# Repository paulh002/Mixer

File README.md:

# Mixer
Simple double balanced mixer and diplexer

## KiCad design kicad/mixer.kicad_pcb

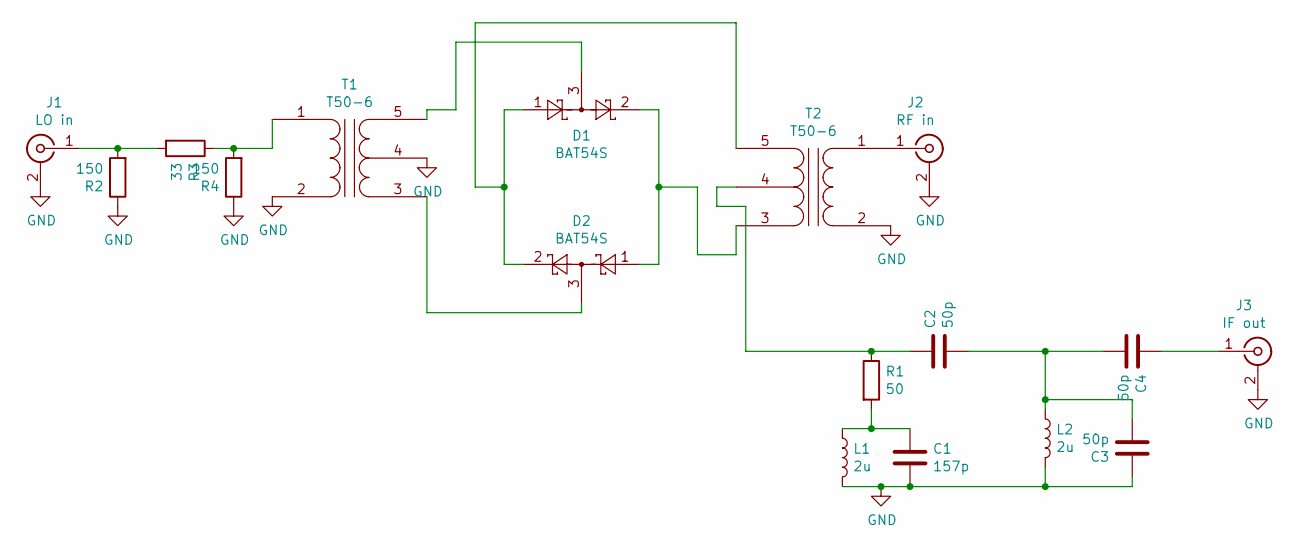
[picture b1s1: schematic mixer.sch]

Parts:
C1: 157p; C_1206_3216Metric_Pad1.42x1.75mm_HandSolder
C2, C3, C4: 50p; C_1206_3216Metric_Pad1.42x1.75mm_HandSolder
D1, D2: BAT54S; SOT-23
J1: LO in; SMA_Amphenol_132134_Vertical
J2: RF in; SMA_Amphenol_132134_Vertical
J3: IF out; SMA_Amphenol_132134_Vertical
L1, L2: 2u; Transformer_Toroid_Horizontal_3S_D14.0mm_Amidon-T50
R1: 50; R_1206_3216Metric_Pad1.42x1.75mm_HandSolder
R2, R4: 150; R_1206_3216Metric_Pad1.42x1.75mm_HandSolder
R3: 33; R_1206_3216Metric_Pad1.42x1.75mm_HandSolder
T1, T2: T50-6; Transformer_Toroid_Horizontal_3S_D14.0mm_Amidon-T50

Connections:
GND: C1.2, C3.1, J1.2 (Ext), J2.2 (Ext), J3.2 (Ext), L1.2, L2.2, R2.1, R4.1, T1.2 (AB), T1.4 (SC), T2.2 (AB)
unnamed: C1.1, L1.1, R1.2
unnamed: C2.1, R1.1, T2.4 (SC)
unnamed: C2.2, C3.2, C4.2, L2.1
unnamed: C4.1, J3.1 (In)
unnamed: D1.1, D2.2, T2.5 (SB)
unnamed: D1.2, D2.1, T2.3 (SA)
unnamed: D1.3, T1.5 (SB)
unnamed: D2.3, T1.3 (SA)
unnamed: J1.1 (In), R2.2, R3.2
unnamed: J2.1 (In), T2.1 (AA)
unnamed: R3.1, R4.2, T1.1 (AA)

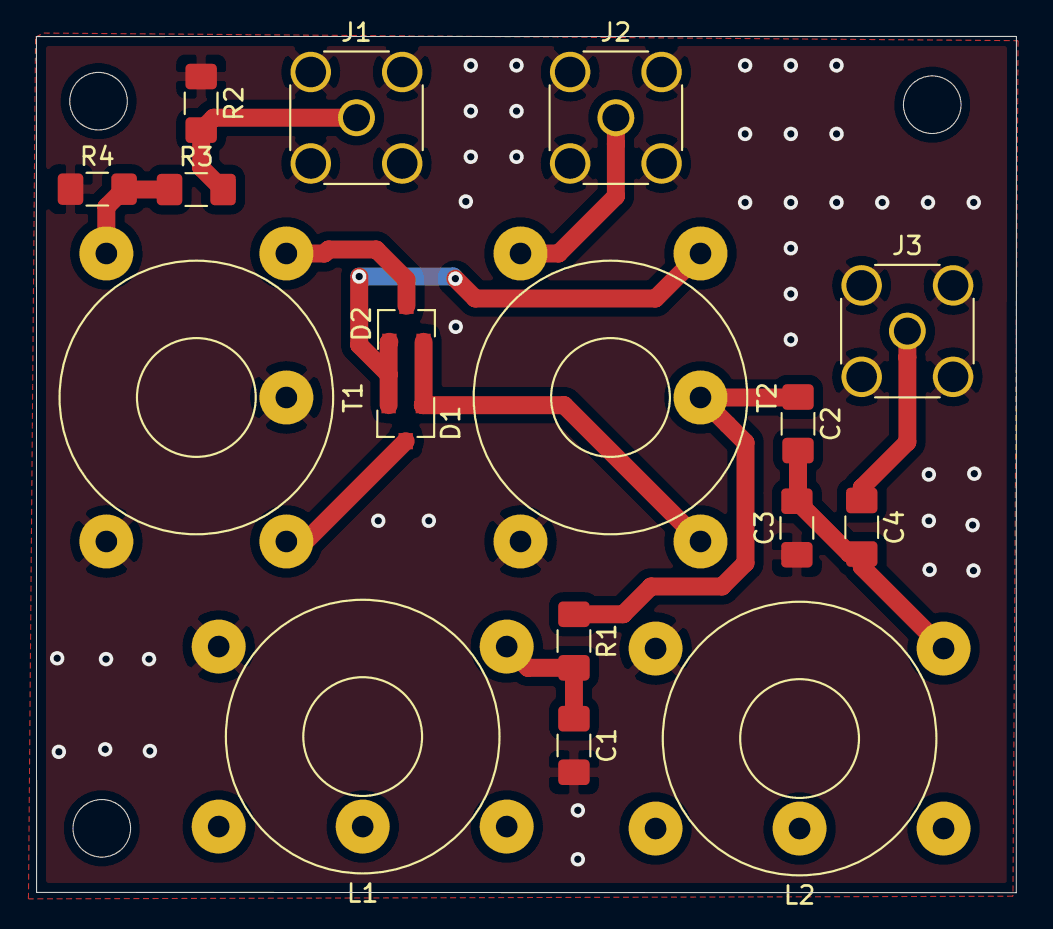
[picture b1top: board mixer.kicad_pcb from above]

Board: 2 copper layers, 54.4 x 47.6 mm, 20 parts (0 on the bottom side), 12 nets.

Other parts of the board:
 : MountingHole_3.2mm_M3
 #2,  #3: MountingHole_3.2mm_M3
